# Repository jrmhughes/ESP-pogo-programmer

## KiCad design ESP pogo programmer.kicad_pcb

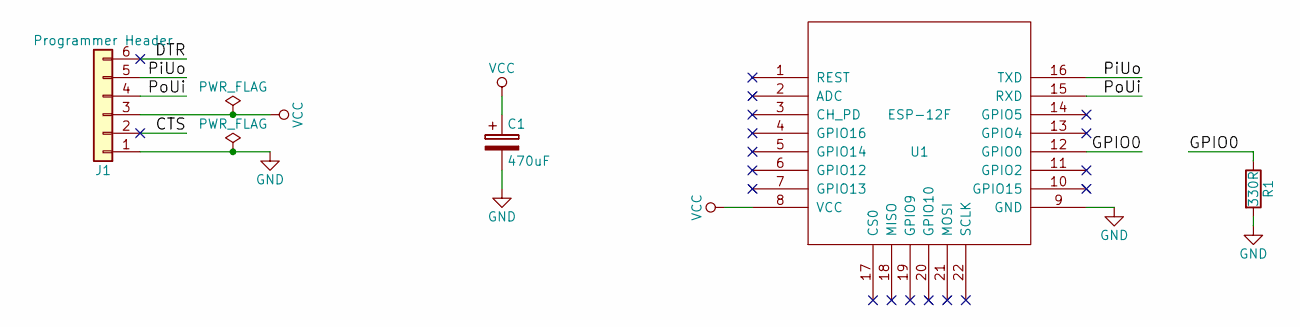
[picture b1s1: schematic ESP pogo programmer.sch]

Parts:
C1: 470uF; CP_Radial_D6.3mm_P2.50mm
J1: Programmer Header; Socket_Strip_Straight_1x06_Pitch2.54mm
R1: 330R; R_Axial_DIN0207_L6.3mm_D2.5mm_P7.62mm_Horizontal
U1: ESP-12F; ESP-12F-pgrm

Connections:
/CTS: J1.2
/DTR: J1.6
/GPIO0: R1.1, U1.12 (GPIO0)
/PiUo: J1.5, U1.16 (TXD)
/PoUi: J1.4, U1.15 (RXD)
GND: C1.2, J1.1, R1.2, U1.9 (GND)
VCC: C1.1, J1.3, U1.8 (VCC)

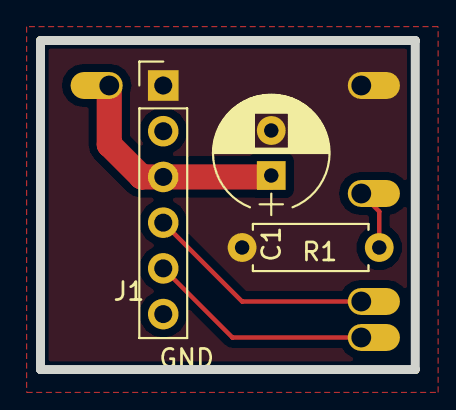
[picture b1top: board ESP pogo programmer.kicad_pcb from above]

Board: 2 copper layers, 20.8 x 18.3 mm, 4 parts (1 on the bottom side), 5 nets.

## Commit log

2018-04-06 Much work on schematic
2018-04-13 Schematic and footprints done
2018-04-13 Board done
2018-04-15 no change
2018-04-16 Various non-final output files
2018-04-17 changed auxilary origin. also output files added.
2018-05-05 create_gcode.py created
    Other changes are not important. create_gcode.py in progress.
2018-05-05 organised gcode block classes
2018-05-05 updated rest of code to use classes
2018-05-05 fixed compile errors
2018-05-05 added method to write output to file
2018-05-05 added append method. FCu is currently local to init_operations function, making it useless.
2018-05-05 added external start and end gcode. seems to be done. just need to insert operations.
2018-05-05 change comments and make it work with python 3
    changed xrange (python2) to range (python 3, also compatible with python 2)
2018-05-06 adjusted track clearances to be more realistic
2018-05-06 ready to print
2018-05-06 it no longer takes over 20 secs. needs neatening
    laser now does holes and outline concurrently.
    replaced string operations with file appends. should do this across the rest of the operations and change the other code to match.
2018-05-07 temporary change to do just cutting
2018-05-07 Swapped incorrect RXD and TXD pins in schematic
    and updated netlist. PCBnew not updated yet.
2018-05-07 swapped false pins in PCBnew
2018-05-07 flipped ESP-12 so its is correct way round
2018-05-07 small changes
    changed edge cut width and position slightly. moved origin to new top right corner.
2018-05-07 moved capacitor down slightly
2018-05-07 reorganised python code. old stuff not yet deleted.
2018-05-07 Neat and working to previous standard
    now need to sort out speeds and drills
2018-05-07 found out about * in strings
    found out about * in strings.
    added '\n' in strings for safety
    added drill delay to gcode_block.fixes
2018-05-07 code looks good
    need to try offsetting the origin from (0, 0) to make end gcode for removal more obvious.
2018-05-07 made delete ends work for drill file
2018-05-08 final version
    holes didn't work
